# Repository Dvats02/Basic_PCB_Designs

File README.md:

This is a basic Printed Circuit Board Design repo where you will get circuits having basic led, Relays, Pinout etc..

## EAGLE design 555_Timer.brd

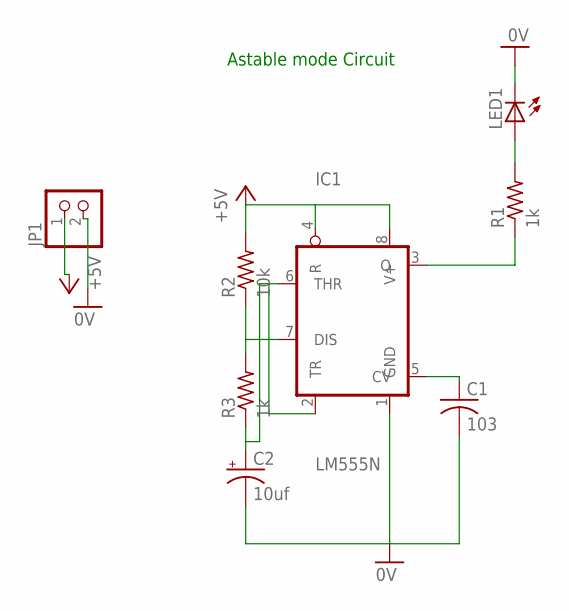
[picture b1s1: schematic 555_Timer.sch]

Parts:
C1: 103; C025-024X044
C2: 10uf; E2-5
IC1: LM555N; DIL08
JP1: PINHD-1X2; 1X02
LED1: LED5MM
R1, R3: 1k; 0207/10
R2: 10k; 0207/10

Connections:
0V: C1.2, C2.-, IC1.1 (GND), JP1.2, LED1.K (C)
+5V: IC1.4 (R), IC1.8 (V+), JP1.1, R2.2
unnamed: C1.1, IC1.5 (CV)
unnamed: IC1.7 (DIS), R2.1, R3.2
unnamed: IC1.3 (Q), R1.1
unnamed: LED1.A, R1.2
unnamed: C2.+, IC1.2 (TR), IC1.6 (THR), R3.1

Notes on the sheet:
Astable mode Circuit

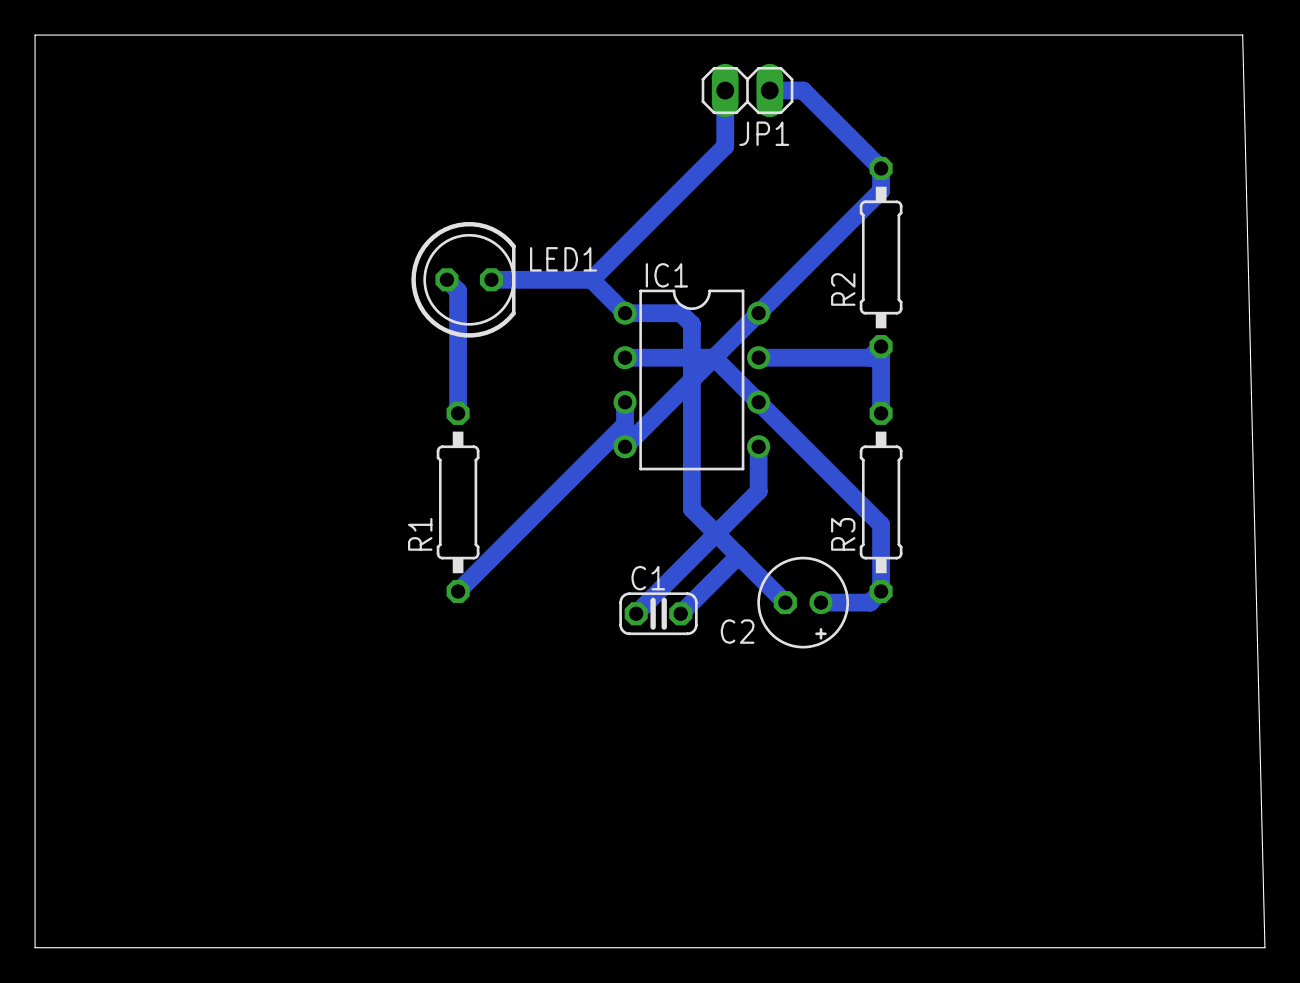
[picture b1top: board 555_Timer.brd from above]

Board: 2 copper layers, 70.2 x 52.1 mm, 8 parts (0 on the bottom side), 7 nets.

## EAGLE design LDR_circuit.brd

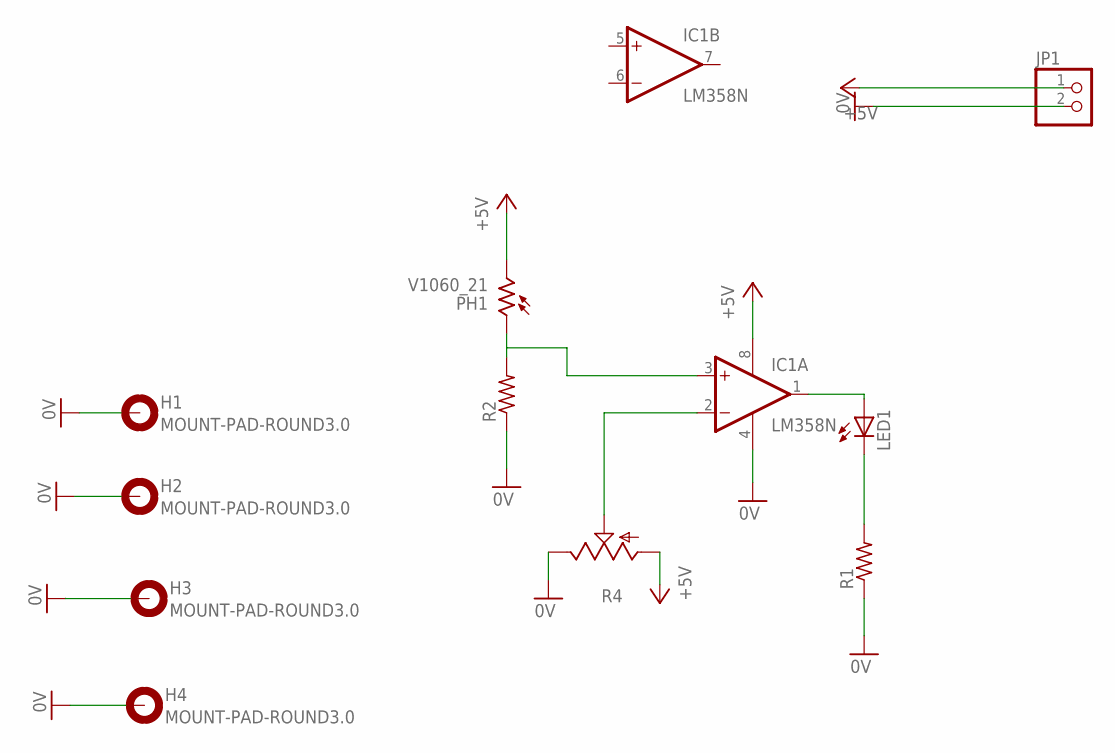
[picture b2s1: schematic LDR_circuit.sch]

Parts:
H1, H2, H3, H4: MOUNT-PAD-ROUND3.0; 3,0-PAD
IC1: LM358N; DIL08
JP1: PINHD-1X2; 1X02
LED1: LED5MM
PH1: V1060_21; TO-5_V10
R1, R2: R-US_0207/10; 0207/10
R4: TRIM_US-CA6V; CA6V

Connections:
0V: H1.B3,0, H2.B3,0, H3.B3,0, H4.B3,0, IC1.4 (V-), JP1.2, R1.1, R2.1, R4.E
+5V: IC1.8 (V+), JP1.1, PH1.2, R4.A
unnamed: LED1.K (C), R1.2
unnamed: IC1.1 (OUT), LED1.A
unnamed: IC1.3 (+IN), PH1.1, R2.2
unnamed: IC1.2 (-IN), R4.S

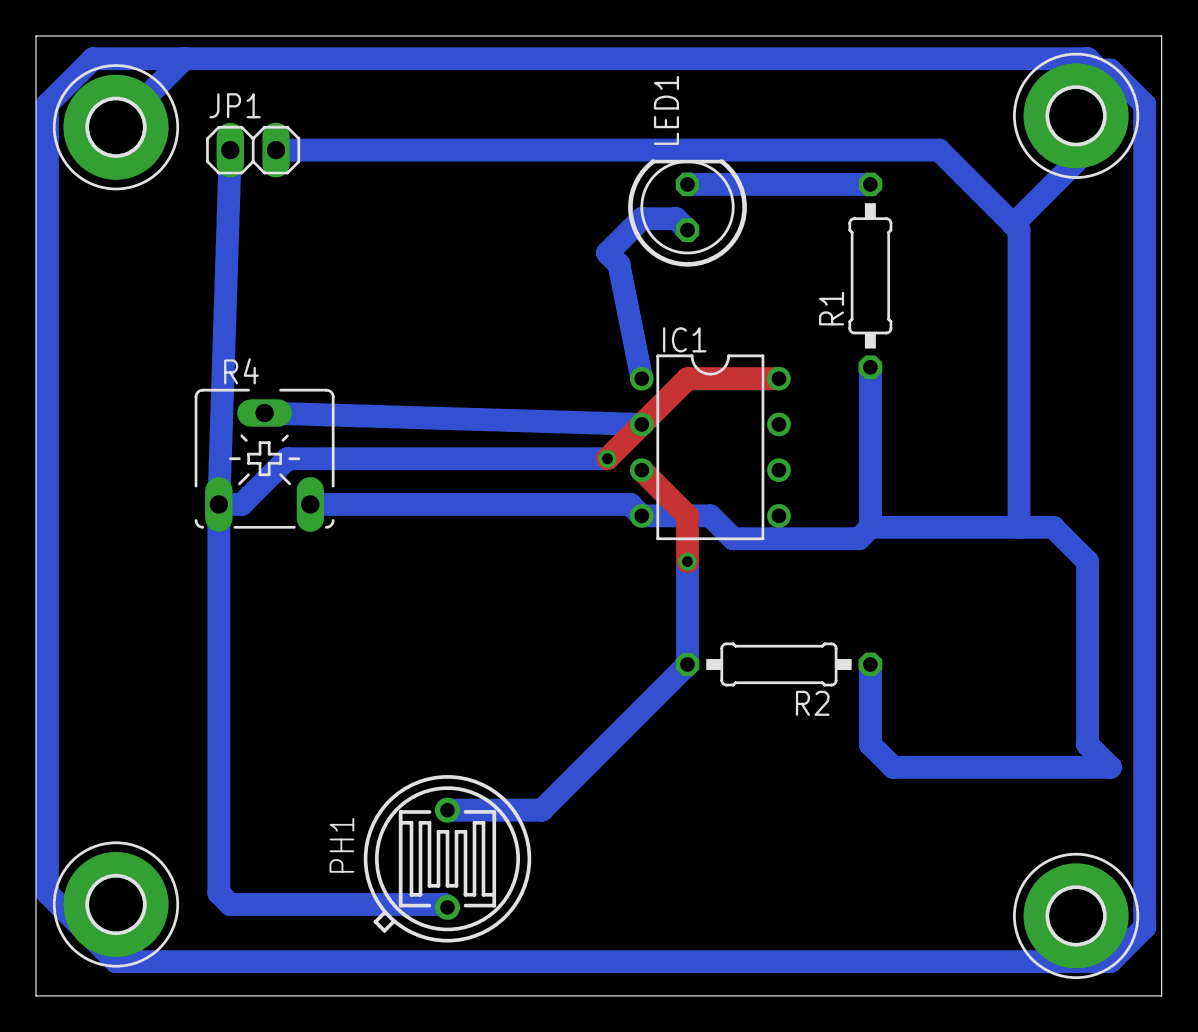
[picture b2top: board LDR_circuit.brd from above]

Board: 2 copper layers, 62.5 x 53.3 mm, 11 parts (0 on the bottom side), 6 nets.

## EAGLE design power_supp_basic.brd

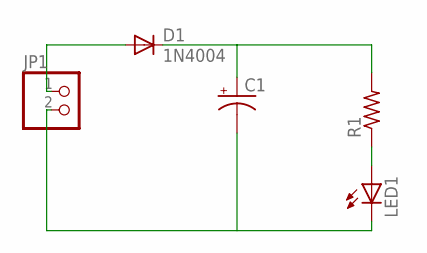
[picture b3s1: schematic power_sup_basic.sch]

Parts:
C1: CPOL-USE3.5-10; E3,5-10
D1: 1N4004; DO41-10
JP1: PINHD-1X2; 1X02
LED1: LED5MM
R1: R-US_0207/10; 0207/10

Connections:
unnamed: D1.A, JP1.1
unnamed: C1.+, D1.C, R1.2
unnamed: LED1.A, R1.1
unnamed: C1.-, JP1.2, LED1.K (C)

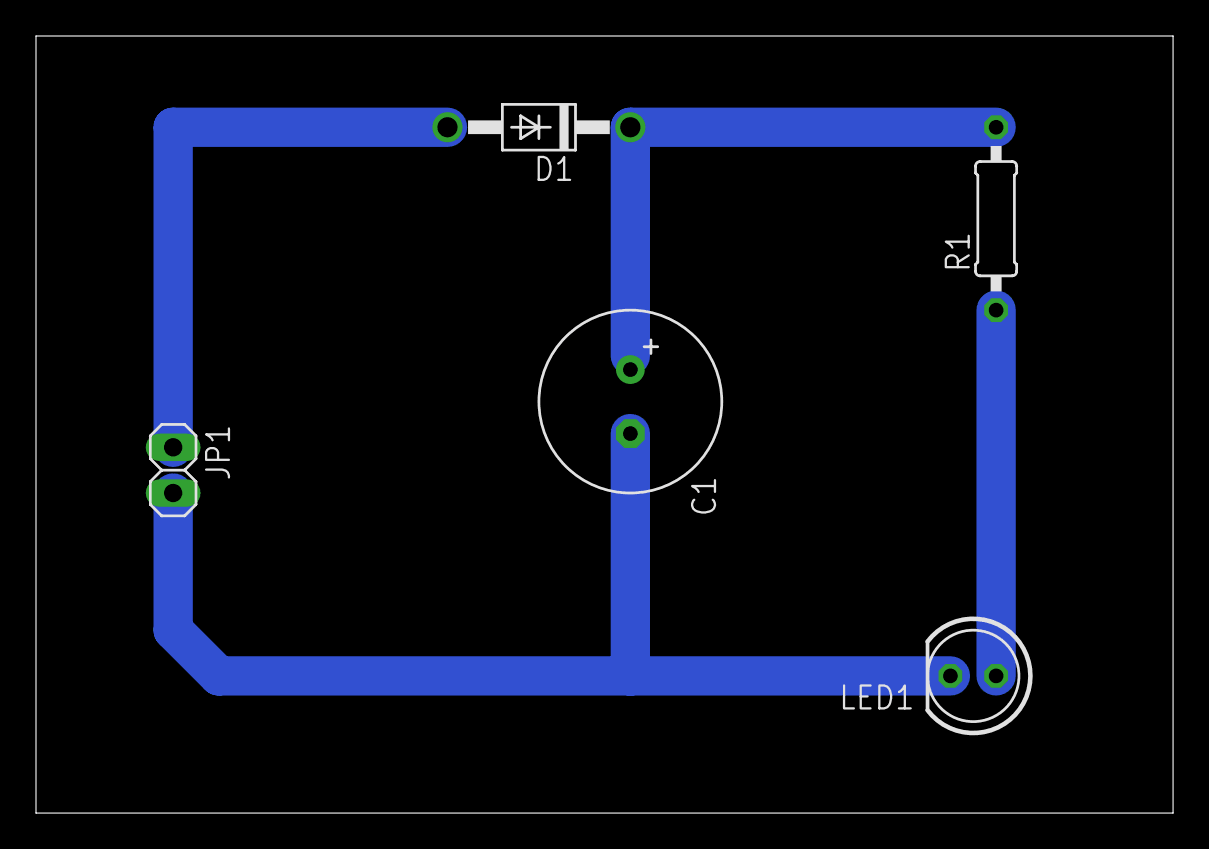
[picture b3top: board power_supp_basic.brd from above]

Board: 2 copper layers, 63.2 x 43.2 mm, 5 parts (0 on the bottom side), 4 nets.

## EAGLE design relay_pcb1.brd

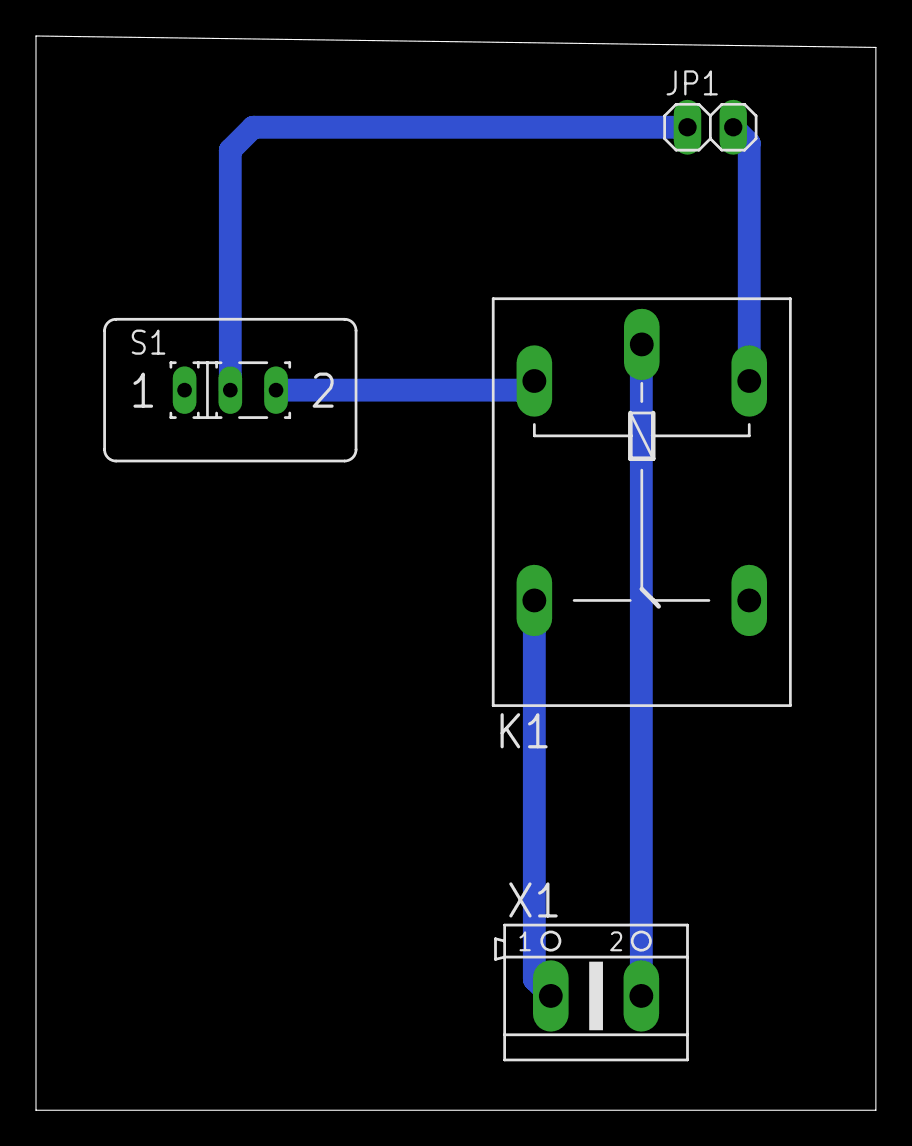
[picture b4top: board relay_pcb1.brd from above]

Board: 2 copper layers, 46.7 x 59.7 mm, 4 parts (0 on the bottom side), 5 nets.

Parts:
JP1: 1X02
K1: G5LE
S1: M251
X1: AK500/2

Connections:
0V: JP1.1, S1.2
+5V: JP1.2, K1.2
unnamed: K1.1, S1.3
unnamed: K1.P, X1.2
unnamed: K1.S, X1.1
